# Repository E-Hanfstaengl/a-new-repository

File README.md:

## 计时消毒口罩盒

### 团队介绍与分工：
**create小组，成员：** 常温新，姜生新，李响，唐志豪，张凯

**电路设计：** 张凯 [*ZK-xyzs*](https://github.com/ZK-xyzs)

**3d建模：** 唐志豪 [*zhihao-tang*](https://github.com/zhihao-tang)

**编程：** 李响 [*Alexander-lx*](https://github.com/Alexander-lx)

**app界面：** 常温新 [*E-Hanfstaengl*](https://github.com/E-Hanfstaengl)

**实物组装：** 姜生新 [*Jsx184477515*](https://github.com/Jsx184477515)

### 设计概念：
疫情期间，规范佩戴口罩是保护身体健康的必要手段，但口罩佩戴时间长短难以把控、消毒方式难以达标使得口罩的防护效果受到一定程度的影响。本小组设计的计时消毒口罩盒旨在提供储存、记录佩戴时间并达到在口罩的有效防护期6小时通过手机app提醒佩戴者更换口罩、对口罩进行紫外线消毒等功能，使口罩的更换和再次利用更加便利。
### 材料清单：

### 程序代码（含消毒部分）
```
int purplePin = 2 ;
int yellowPin = 4 ;
int greenPin = 5 ;
int redPin = 7 ;

int speakPin = 6 ;

int pressPin = 3 ;
int clickPin = 8 ;

int judge = 1 ;
int kg = 1;
int timerOne = 0 ;
int timerTwo = 0 ;
int timerThree = 0 ;
int limit = 1000*60*60*6;

void setup() {
pinMode(purplePin, OUTPUT);
pinMode(redPin, OUTPUT);
pinMode(yellowPin, OUTPUT);
pinMode(greenPin, OUTPUT);
pinMode(speakPin, OUTPUT);
pinMode(pressPin, INPUT_PULLUP);
pinMode(clickPin, INPUT_PULLUP);
}

void loop() {

if ( digitalRead(pressPin) == LOW){
  judge = 0;
  digitalWrite(yellowPin, HIGH);
  delay(30000);
}

if (judge == 0) {
  digitalWrite(purplePin, HIGH);
  digitalWrite(yellowPin, HIGH);
  delay(1000*60*30);
  digitalWrite(purplePin, LOW);
  digitalWrite(yellowPin, LOW);
  digitalWrite(speakPin, HIGH);
  digitalWrite(greenPin, HIGH);
  delay(10000);
  digitalWrite(speakPin, LOW);
  digitalWrite(greenPin, LOW);
  judge = 1;
}

if ( digitalRead(clickPin) == LOW){
  if ( kg == 1) {
    kg = 0 ;
    timerOne = millis();
  }else {
      digitalWrite(greenPin, HIGH);
      delay(10000);
      digitalWrite(greenPin, LOW);
      kg = 1;
     }  
}

if (kg == 0){
 timerTwo = millis();
 timerThree = timerTwo - timerOne;
  if (timerThree >= limit){
    digitalWrite(redPin, HIGH);
    digitalWrite(speakPin, HIGH);
    delay(10000);
    digitalWrite(redPin, LOW);
    digitalWrite(speakPin, LOW);
    kg = 1;
  }
}

}  
```
### 程序代码（含显示时间部分）
```
#include<LiquidCrystal.h>
#define buzzer 4
#define BUTTON 5
#define LED 9//消毒完毕提示灯
LiquidCrystal lcd(2,3,12,11,10,13);
int a=0;//时间设定
int b=0;
int c=0;
int val=0;//储存紫外灯按钮状态
int old_val=0;
int state=0;//0紫外灯关闭1打开
void setup() {
  lcd.begin(16,2);
  lcd.print("Youhaveusedfor:");
  pinMode(buzzer,OUTPUT);
  for(int UVLED=6;UVLED<=8;UVLED++){
   pinMode(UVLED,OUTPUT);
   }
   pinMode(LED,OUTPUT);
  pinMode(BUTTON,INPUT);
}
void loop(){
lcd.setCursor(0,1);//以下为计时 显示以及蜂鸣器提醒
  if(millis()<=216000000){
  if(millis()<=60000){a=0;b=0;c=millis()/1000;}
  if((millis()>60000)&&(millis()<=3600000)){
    a=0;
    b=int (millis()/60000);
    c=(millis()-(60000*b))/1000;
  }
  if((millis()>3600000)){
    a=int (millis()/3600000);
    b=int ((millis()-a*3600000)/60000);
    c=(millis()-(3600000*a)-(60000*b))/1000;
  }
  lcd.print(a);
  lcd.setCursor(2,1);
  lcd.print(":");
  lcd.setCursor(3,1);
  lcd.print(b);
  lcd.setCursor(5,1);
  lcd.print(":");
  lcd.setCursor(6,1);
    lcd.print(c);}
  else{lcd.print("TIME IS UP");
      digitalWrite(buzzer,HIGH);}//以下为按键控制紫外灯亮起
      val=digitalRead(BUTTON);//读取按钮输入并存储，检查变化情况
  if((val==HIGH)&&(old_val==LOW)){
    state=1-state;
    delay(1000);
    }
    old_val=val;//暂存
    if(state==1){
      for(int UVLED=6;UVLED<=8;UVLED++){
       digitalWrite(UVLED,HIGH);}
       digitalWrite(LED,LOW);
        delay(900000);//消毒时间15分钟
        for(int UVLED=6;UVLED<=8;UVLED++){
       digitalWrite(UVLED,LOW);}
       digitalWrite(LED,HIGH);
       delay(300000);
       }
      else{
        for(int UVLED=6;UVLED<=8;UVLED++){
       digitalWrite(UVLED,LOW);}
       delay(600);
        }}
```
[TIMER](https://github.com/E-Hanfstaengl/a-new-repository/blob/master/%E4%BB%A3%E7%A0%81%E8%AE%A1%E6%97%B6%E5%92%8C%E6%B6%88%E6%AF%92%26%E7%AE%80%E6%98%93%E5%AE%9E%E7%89%A9%E6%BC%94%E7%A4%BA/TIMER.brd)
>**简易实物演示**
>
>
>[视频链接](website/uvled.mp4)

***
>消毒盒子的紫外线消毒和口罩佩戴提醒功能，(暂时通过盒子本身蜂鸣器提醒用户)经查询可知
1. 对眼睛皮肤有害，解决方法：把待消毒物品放入盒子，关闭盒子后按开关，紫外灯亮起，开始消毒。
消毒过程中不能打开盒子，消毒完毕紫外灯关闭，待盒子上绿色提示灯亮起，用户将已消毒物品取出。
之后用户如果想对其他物品消毒，需要在绿灯亮起时，放入待消毒物品。
2. 紫外灯在250-260nm波长能起到较好杀菌作用，选用个波长275nm辐射通量5mw的紫外LED，照射剂量为为300J/m2时才能做到有效杀菌，
根据盒子大小估算得出13min左右可做到消毒，因此设定消毒时长为15min。

### 电路图

### 三维渲染图
.png)
.png)
.png)
.png)
.png)
.png)
.png)
.png)
.png)
.png)
.png)

### app界面

### 实物展示
.jpg)
.jpg)
.jpg)

### 相关信息
[凿物网展示页面](https://zaowu.fun/p/5ee777be9c5fec674b69016f)

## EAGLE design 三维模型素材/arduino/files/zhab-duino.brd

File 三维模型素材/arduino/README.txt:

.:                     :,                                          
,:::::::: ::`      :::                   :::                                          
,:::::::: ::`      :::                   :::                                          
.,,:::,,, ::`.:,   ... .. .:,     .:. ..`... ..`   ..   .:,    .. ::  .::,     .:,`   
   ,::    :::::::  ::, :::::::  `:::::::.,:: :::  ::: .::::::  ::::: ::::::  .::::::  
   ,::    :::::::: ::, :::::::: ::::::::.,:: :::  ::: :::,:::, ::::: ::::::, :::::::: 
   ,::    :::  ::: ::, :::  :::`::.  :::.,::  ::,`::`:::   ::: :::  `::,`   :::   ::: 
   ,::    ::.  ::: ::, ::`  :::.::    ::.,::  :::::: ::::::::: ::`   :::::: ::::::::: 
   ,::    ::.  ::: ::, ::`  :::.::    ::.,::  .::::: ::::::::: ::`    ::::::::::::::: 
   ,::    ::.  ::: ::, ::`  ::: ::: `:::.,::   ::::  :::`  ,,, ::`  .::  :::.::.  ,,, 
   ,::    ::.  ::: ::, ::`  ::: ::::::::.,::   ::::   :::::::` ::`   ::::::: :::::::. 
   ,::    ::.  ::: ::, ::`  :::  :::::::`,::    ::.    :::::`  ::`   ::::::   :::::.  
                                ::,  ,::                               ``             
                                ::::::::                                              
                                 ::::::                                               
                                  `,,`

https://www.thingiverse.com/thing:2328572
Raspberry Pi Zero HAB Shield Adapter by Anathae is licensed under the Creative Commons - Attribution - Non-Commercial - Share Alike license.
http://creativecommons.org/licenses/by-nc-sa/3.0/

# Summary

Arduino shield that uses a Raspberry Pi Zero as a component to add a compact in place keyboard, monitor, mouse interface to an Arduino project.

# How I Designed This

## Corrections

Discovered tonight, the schematic and board layout that I uploaded originally did not have the seven pin header that allows both setting the logic voltage level for the arduino as well as allowing the Zero to power the Arudino, but only had a four pin header for allowing the Zero to power the Arduino.  Uploaded the correct files.  Sorry for the confusion.

## Design notes.

I have a Pi Alamode addon for the original Raspberry Pi B.  I also have a Raspberry Pi Zero.  This is my take on taking the combination to at least one extreme.

No 3D files in the object, just a screen grab from Sketchup from file I used to check fitment of the shield board to the Zero.

I took the measurements from my reference model of the [Zero](http://www.thingiverse.com/thing:1612021) and used them to add the through mounting holes as well as the placement of the two by twenty 0.1 inch pitch pin header on the Zero in the Eagle CAD design.  This, in combination with printing out the resulting pcb and checking the placement of the OTG cable and the mini HDMI to HDMI adapter allowed me to find a good placement for the Zero as well as placement for the components on the board.

Single sided PCB are fairly easy for a DIYer to create at home.  By going with an eight pin dual n-channel MOSFET and four 1206 surface mount pull up resistors, I was able to get the entire circuit on one side with no jumpers required.  To do so, I had to route some of the signals in between the pads for the resistors.  

The seven pins near the one end of the board are used to select logic voltage of the Arduino board as well as select if the 5 and 3.3 volts from the Zero is passed on to the Arduino or not.

This board basically maps the RX/TX pins of the Zero to the TX/RX pins of the Arduino.  One complication of this is that the Arudino Uno (at least up to and including the R3 version) has 5 volt TTL serial, but the Zero had 3.3 volt TTL serial.  

There are a couple of ways of dealing with this, but the design used in this iteration of this board, I wired up an N-Channel enhancement MOSFET as a bidirectional logic level shifter between the Arduino and the Zero.  If pins 1 and 2 of the seven pin male pin header are shorted with a jumper, the 3.3 volt supply of the Zero is routed to the Arduino side of the level shifter.  with pins 2 and 3 of the header shorted, the 5 volt supply of the Zero is routed to the Arduino side of the level shifter.

Starting with the revision 3 of the Arduino Uno, a pin that is held at the logic voltage level of the Arduino has been added.  On the Arudino Due, this pin is at 3.3 volts, and on the Arduino Uno R3, it is at 5 volts.  If I had been willing to use jumpers, it might have been possible to route this pin from the Arduino to the logic level shifter to allow automatic selection of the IO voltage level by the shield from the Arduino, but for this iteration of this board I decided single sided was more important.

Pins 4 and 5 of the 7 pin pin header shorted out connect the 5 volt supply of the Zero and the Arduino.  Pins 6 and 7 shorted out connect the 3.3 volt supply.  There are limits to the Zero's power supply and you should check the power requirements of your stack of Arduino and shields to make sure you can power it from the Zero if you decide to do this.  The rather short look I did online convinced me that it would be a good idea to add these jumpers to allow for either powering the Zero and the Arduino independently, or allowing the Zero to power the Arduino.

The cut out in the corner of this shield is to allow for space around the mini HDMI adapter on the Zero.  This provides no strain relief.  Best practice would be to design a case for this that properly supports the adapter, or perhaps using a mini HDMI to full size HDMI cable instead to try and prevent the surface mounted HDMI port on the Zero from getting ripped off due to deflection of the video cable.

One of the mounting holes for the Arduino ends up being very close to being directly under the OTG port on the Zero.  A right angle OTG cable might be short enough in that access that you can use a stand off on either side of this shield to mount it to other shields in your stack.  The power port on the Zero will require a right angle cable to be plugged in.  From my measurements (haven't confirmed it yet, sorry) the right angle USB A to USB B Micro cable from StarTech should fit in this location.

The fourty pin (two by twenty) pin header connecting the Zero to this shield will likely have to be put in "upside down" with the long side of the pins going trough the shield, and the short side soldered down through the top size of the Zero.  With this pin header in it's normal orientation, it may interfere with signal traces on the bottom of shields above this board.  A right angle seven pin header should be used for the voltage selection as well for similar reasons.  To keep this header from preventing one of the mounting holes on the Arduino from being used, it will have to point toward the Zero.  If requested, I can move this header down so that is can point out from between the two mounting holes on this end.

I tried to place the voltage selection header far enough away from the camera port on the Zero to allow for it to be used.

# Comments Requested

Constructive comments on this design greatly appreciated.

If you like this idea and can think of a stack of boards that you would like to use it in, I'd be thrilled to find out.  Myself, I plan to use it with and Arduino Uno, and the Pronteer Arduino CNC shield.

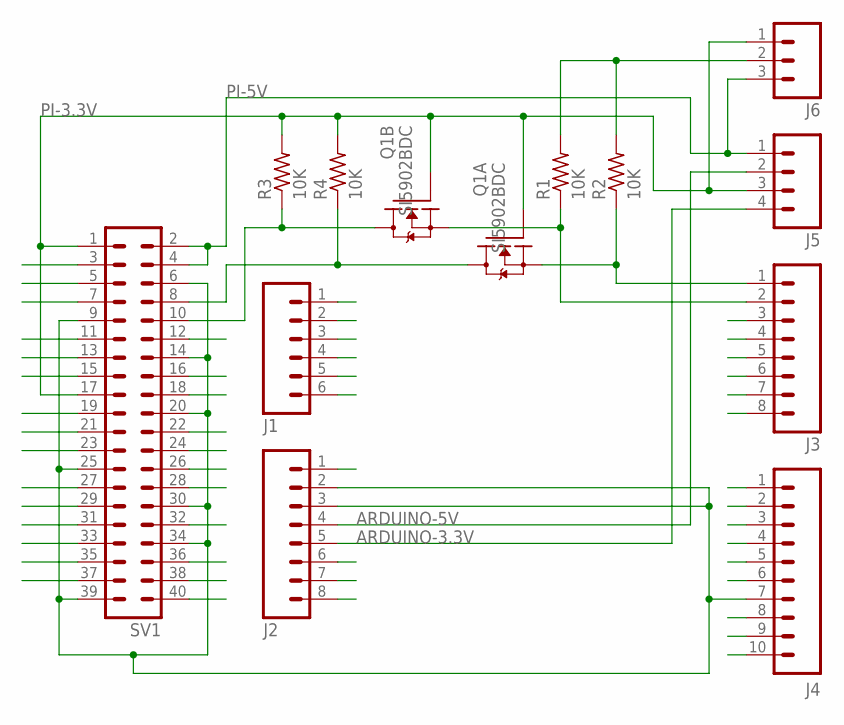
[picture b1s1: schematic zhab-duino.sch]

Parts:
J1: M06NO_SILK_FEMALE_PTH; 1X06_NO_SILK
J2, J3: M08NO_SILK_FEMALE_PTH; 1X08_NO_SILK
J4: M10NO_SILK_PTH_FEMALE; 1X10_NO_SILK
J5: M04NO_SILK_ALL_ROUND; 1X04_NO_SILK_ALL_ROUND
J6: M031X03_NO_SILK; 1X03_NO_SILK
Q1: SI5902BDC; 1206-8CHIP-FET
R1, R2, R3, R4: 10K; M1206
SV1: MA20-2

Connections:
ARDUINO-3.3V: J2.5, J5.4
ARDUINO-5V: J2.4, J5.2
GND: J2.2, J2.3, J4.7, SV1.6, SV1.9, SV1.14, SV1.20, SV1.25, SV1.30, SV1.34, SV1.39
GPIO2: SV1.3
GPIO3: SV1.5
GPIO4: SV1.7
GPIO5: SV1.29
GPIO6: SV1.31
GPIO7: SV1.26
GPIO8: SV1.24
GPIO9: SV1.21
GPIO10: SV1.19
GPIO11: SV1.23
GPIO12: SV1.32
GPIO13: SV1.33
GPIO15: J3.2, Q1.3 (S), R1.1
GPIO16: SV1.36
GPIO17: SV1.11
GPIO18: SV1.12
GPIO19: SV1.35
GPIO20: SV1.38
GPIO21: SV1.40
GPIO22: SV1.15
GPIO23: SV1.16
GPIO24: SV1.18
GPIO25: SV1.22
GPIO26: SV1.37
GPIO27: SV1.13
ID_SC: SV1.28
ID_SD: SV1.27
unnamed: Q1.5 (D), Q1.6 (D), R3.1, SV1.10
unnamed: Q1.7 (D), Q1.8 (D), R4.1, SV1.8
unnamed: J6.2, R1.2, R2.2
unnamed: J3.1, Q1.1 (S), R2.1
PI-3.3V: J5.3, J6.1, Q1.2 (G), Q1.4 (G), R3.2, R4.2, SV1.1, SV1.17
PI-5V: J5.1, J6.3, SV1.2, SV1.4

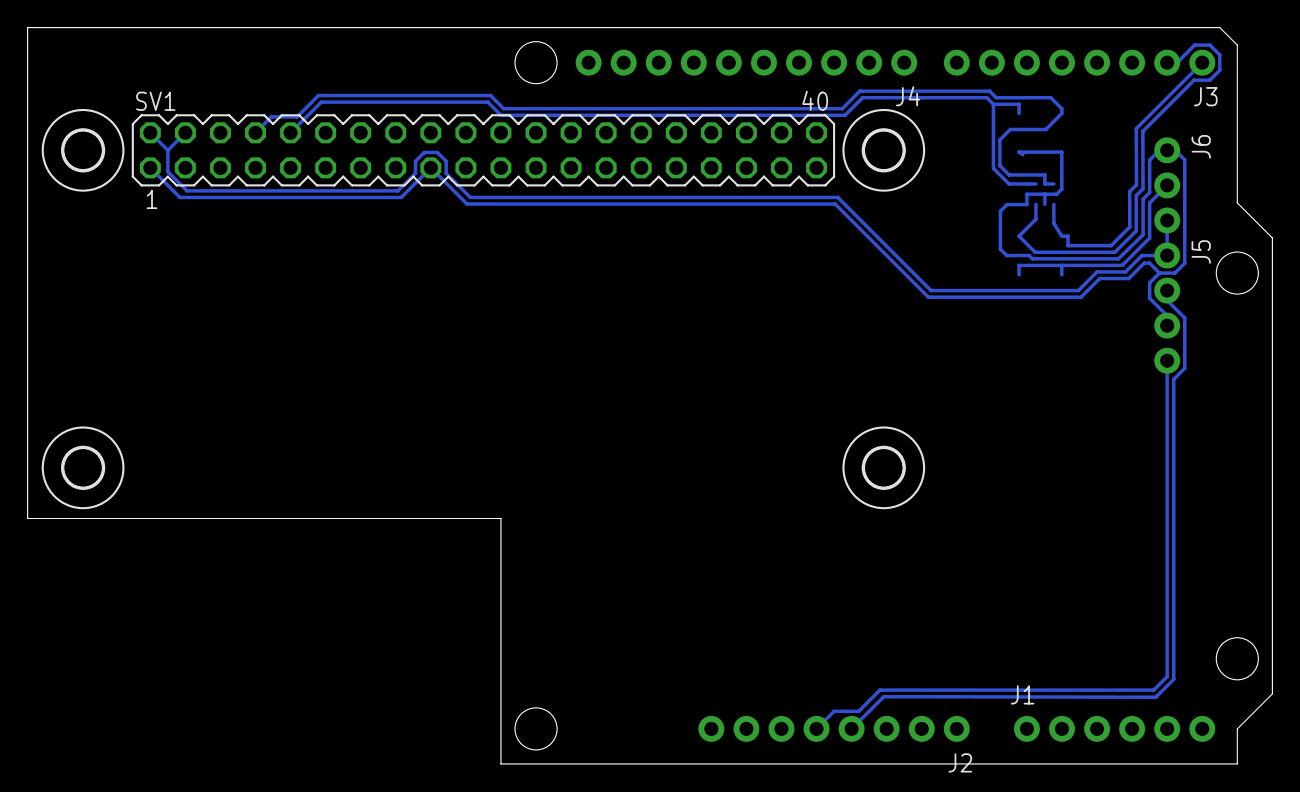
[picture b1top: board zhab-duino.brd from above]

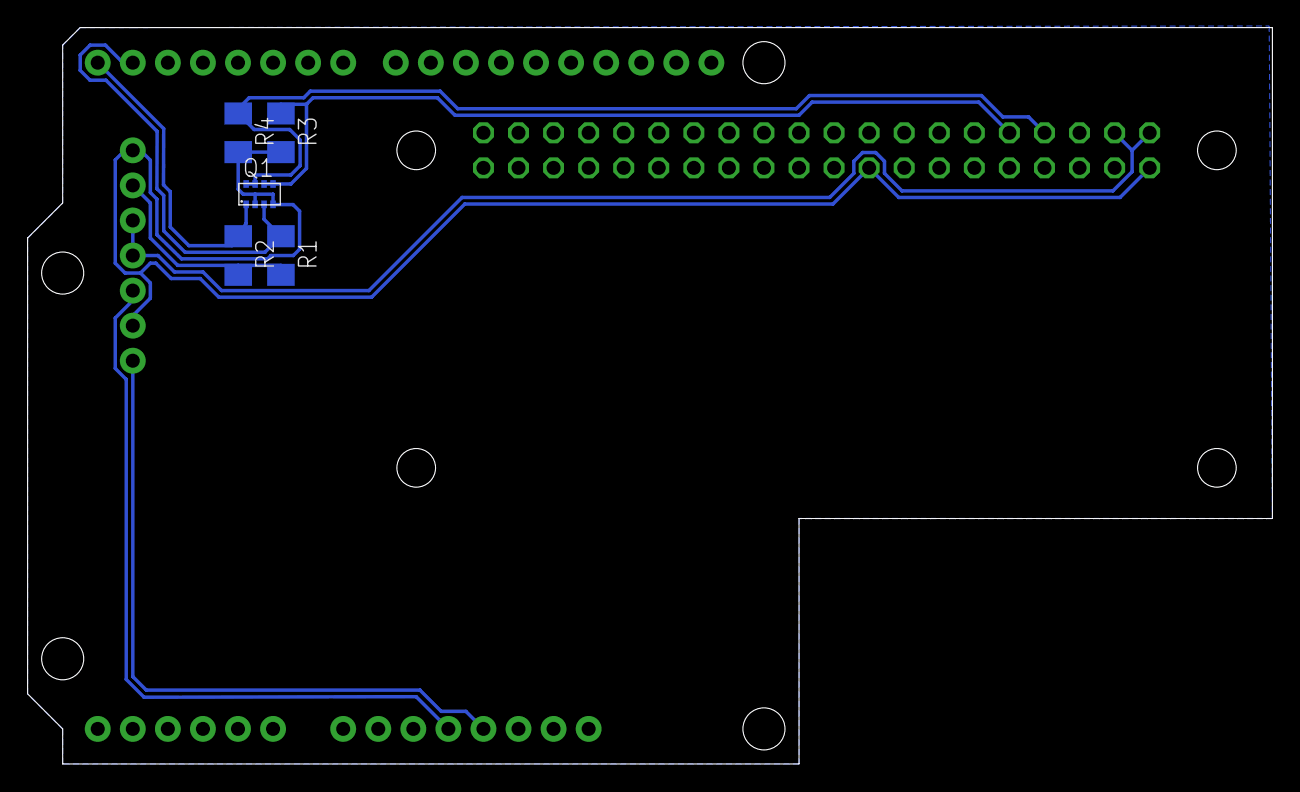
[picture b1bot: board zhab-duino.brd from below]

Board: 2 copper layers, 90.2 x 53.3 mm, 16 parts (5 on the bottom side), 10 nets.

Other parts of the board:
U$1, U$2, U$3, U$4: 2,8

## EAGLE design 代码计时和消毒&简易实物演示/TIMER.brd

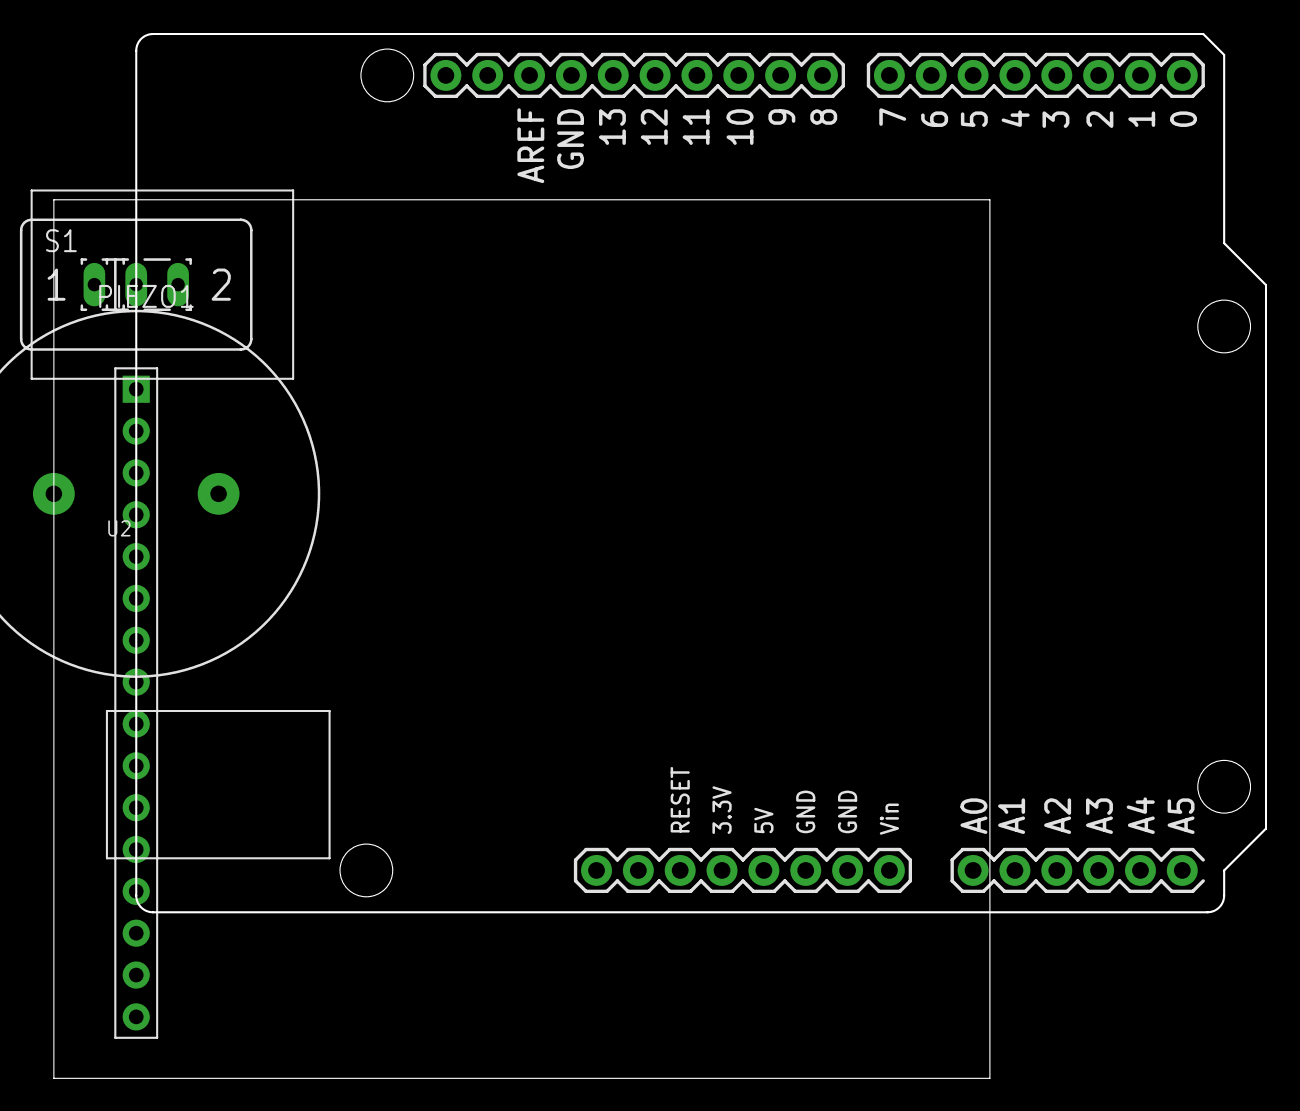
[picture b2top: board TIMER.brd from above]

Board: 2 copper layers, 73.6 x 63.4 mm, 4 parts (0 on the bottom side), 10 nets, no tracks yet.

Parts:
PIEZO1: PIEZO-22MM
S1: M251
U1: ARDUINO_UNO
U2: 1X16P-2.54-2.54-11.6-3.0-BLACK-MALE

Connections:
unnamed: U1.13, U2.14
unnamed: S1.2, U2.3
unnamed: S1.1, U1.5V, U2.2
unnamed: U1.10, U2.13
unnamed: U1.11, U2.12
unnamed: U1.12, U2.11
unnamed: U1.3, U2.6
unnamed: U1.2, U2.4
unnamed: PIEZO1.P$1, U1.4
unnamed: PIEZO1.P$2, S1.3, U1.GND.., U2.1, U2.5

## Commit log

2020-03-16 姜生新的第1次作业
    姜生新的第1次作业3D模型
2020-03-16 姜生新的第1次作业
2020-03-17 finished my homework
2020-03-28 张凯编写的程序
    编的很烂，求大佬修改
2020-03-28 a try with processing
    You can press 'w' 'a' 's' 'd' to control the course of the rectangle.
2020-04-14 arduino 练习
2020-04-14 搞错地方了
2020-06-11 三维建模
2020-06-13 timer&sterilizer
    消毒盒子的紫外线消毒和口罩佩戴提醒功能，(暂时通过盒子本身蜂鸣器提醒用户)经查询可知
    1.对眼睛皮肤有害，解决方法：需要消毒时，把待消毒物品放入盒子，关闭盒子后按开关，紫外灯亮起，开始消毒。消毒过程中不能打开盒子，消毒完毕，紫外灯自动关闭，待盒子上提示灯亮起，用户将已消毒物品取出。
    2.紫外灯在250-260nm波长能起到较好杀菌作用，选用4个波长275nm辐射通量5mw的紫外LED，照射剂量为为300J/m2时才能做到有效杀菌，根据盒子大小估算得出10min左右可做到消毒，因此设定消毒时长为15min
2020-06-14 基本功能
2020-06-14 修改
    第一次修改
2020-06-14 基本功能电路图与程序
    更改了一下
2020-06-14 Create 三维模型 v7.f3z
    第七版三维建模
2020-06-14 三维渲染图最终版补充
    三维渲染图最终版补充
2020-06-14 基本消毒功能程序与电路图
    更改了一下
2020-06-15 代码计时和消毒&简易实物演示
2020-06-16 实物及app图

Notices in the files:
parts and their libraries:
SparkFun-Connectors: Licensing: Creative Commons ShareAlike 4.0 International - https://creativecommons.org/licenses/by-sa/4.0
